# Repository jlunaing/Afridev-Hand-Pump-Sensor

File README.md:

# Monitoring System for the Afridev Hand Pump

## Overview

[Source code](src), [circuit schematic and board files](pcb), and [**technical report**](docs) of a proof-of-concept electronic system to monitor the status of the Afridev model of hand pumps.

## Introduction

Different companies, non-profit organizations, and NGOs have implemented water projects in several regions of Africa. One of the most common projects are hand pumps for water wells. A challenge that is presented once these projects are concluded and used by the local residents are that there is no regular maintenance of these hand pumps due to communication difficulties with the local communities. For instance, in most of the Democratic Republic of the Congo (DRC), the lack of cellular signal and internet connection makes it more difficult for repair teams to know when the hand pumps need repair or maintenance. 

The objective of this project is to propose a system that can reduce the time between pump failure and repair by developing a reliable failure detection measuring system that will inform a user when a pump need attention from a repair team. The system will collect data on pump usage and water flow rate estimation to be accessed remotely.

The reduction in hand pump repair time would increase the consistency of well water available to people in the remote areas like the DRC.

## Technical Background

Currently, there are no commercially available options for well pump sensors with the capabilities to detect pump function, monitor water flow rate, and transmit data internationally. However, open-source systems of a similar nature have been developed by other organizations. A notable one is [Charity: Water](https://www.charitywater.org/), a non-profit serving several developing countries through community water projects and sanitation efforts. Their [sensors](https://www.charitywater.org/our-work/sensors)&mdash;which can be retrofitted onto the Afridev, Tapstand, and India Mark II hand pump models&mdash;are able to collect data on the quantity of water being pumped from a well. The gathered data is transmitted to the cloud weekly via cellular networks, where it is stored, processed, and made viewable by an application running on Amazon Web Services (AWS). The Afridev model appears to have been developed from 2016 to 2020 by Intelligent Product Solutions (IPS), while the India Mark II sensor was developed in 2021 by TwistThink over the course of at least a year.

Extensive documentation for the Afridev and India Mark II models of the sensor is available on [GitHub](https://github.com/charitywater/india-mark-ii-sensor). Charity: Water's third generation Afridev hand-pump sensor expands on its predecessors with the ability to gather GPS, temperature, and device performance information. A more recent model, the India Mark II sensor, adds to these capabilities with additional stroke and humidity sensors. It costs $250 to build and maintain for its battery-limited 10-year lifespan and can collect ten million data points over a 24-hour period. This data is continually analyzed through Charity: Water's AWS backend, where personalized emails are dispatched to monitoring teams daily. Design specifications for Charity: Water's sensors are available from open source and served as an initial reference for this design.

The Charity: Water sensors all use a similar strategy to measure water flow rate. During a pumping cycle, water is brought into a chamber where its depth is measured by a series of capacitive sensors. From this, the quantity per pump&mdash;and therefore average flow rate&mdash;can be accurately estimated. While functional, this method has a few weaknesses. The capacitive sensors are highly sensitive to environmental changes such as temperature variation and require frequent (multiple per hour) automated calibrations to maintain measurement accuracy. Moreover, the sensor has an upper limit on the amount of flow it can measure per pump&mdash;any output over the chamber volume cannot be measured. With this setup, Charity: Water claims a 20% tolerance for the calculated flow rate, which was improved to 5% by IPS. More information can be found [here](https://github.com/charitywater/afridev2-sensor/blob/master/software/architecture%20and%20analysis/charity%20water%20AfriDev%20sensor%20algorithm%20v.2.pdf). 

In addition to the common water sensing strategy, both sensors also feature a cellular module to communicate with Charity: Water's cloud infrastructure, GPS to provide positioning, and battery power of undisclosed capacity. It is claimed that the India Mark II sensor can remain operational for up to ten years. While cellular communication is available in some areas of the DRC, coverage is sparce outside of urban settlements. See the [network coverage maps](https://www.gsma.com/coverage/#88) for details. This makes the use of Global System for Mobile Communications (GSM) technology difficult to implement for the pump distribution in the DRC. Satellite communication is a more reliable alternative, with coverage in the DRC by telecommunications infrastructure providers such as Globalstar, Swarm, and Astrocast. For instance, [Globalstar's satellite networks](https://www.globalstar.com/en-us/products/iot/stx3) cover the entirety of the DRC, where this monitoring sensor can be implemented.

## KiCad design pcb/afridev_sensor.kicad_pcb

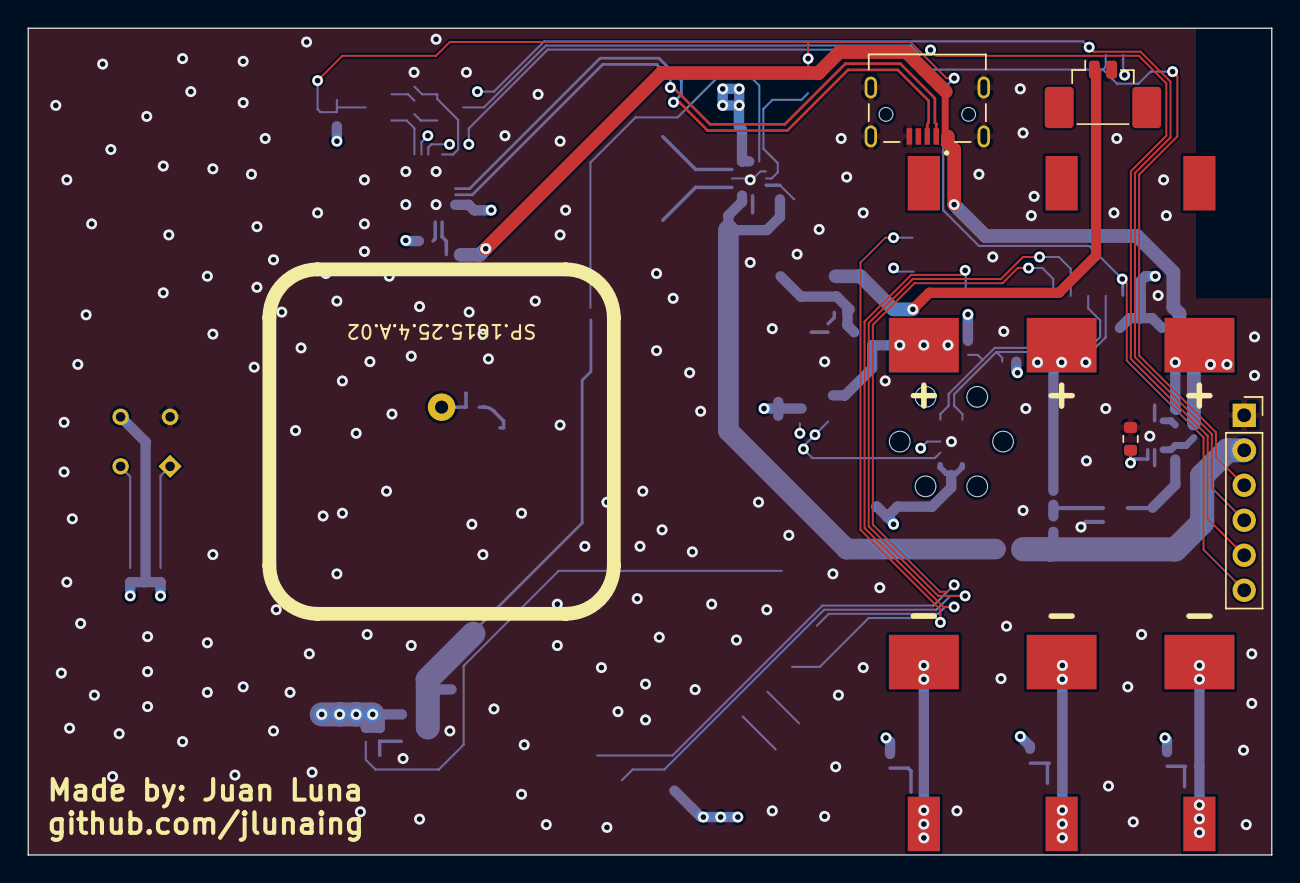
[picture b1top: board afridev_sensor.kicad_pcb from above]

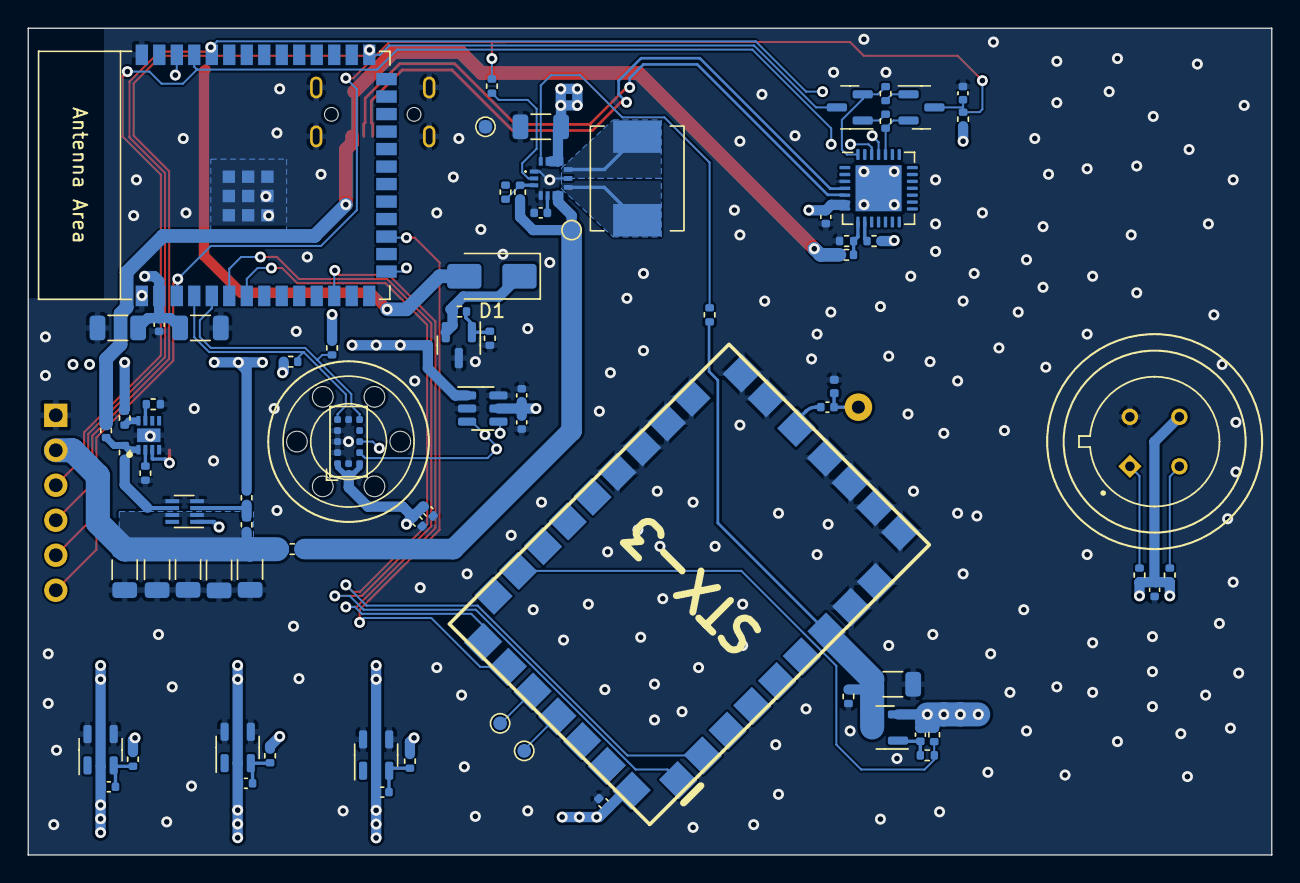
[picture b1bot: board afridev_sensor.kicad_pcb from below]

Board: 4 copper layers, 90.2 x 60.0 mm, 86 parts (78 on the bottom side), 54 nets.

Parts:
AE1: Antenna; ANT_SP.1615.25.4.A.02
BT1, BT2, BT3: Battery_Cell; Keystone 56
C1, C2, C6, C15, C17, C20, C21, C26, C28: 22uF; C_1206_3216Metric
C3, C8, C9, C10, C11, C14, C16: 0.1uF; C_0402_1005Metric
C4, C12, C18, C19, C27: 1uF; C_0402_1005Metric
C5: 4.7uF; C_0402_1005Metric
C7: 10uF; C_0402_1005Metric
C13: 33pF; C_0402_1005Metric
D1: D; D_SMA
H1: MountingHole; VlVenting
IC1: LM66200DRLR; SC-70-8
IC2: MAX77827AEFD+T; MAX77827AEFD
IC3: BQ25170DSGR; SON50P200X200X80-9N
J2: USB_B_Micro; AMPHENOL_GMCB05801124EU
L2: 33nH; L_0402_1005Metric
L4: 1uH; L_Neosid_SM-PIC0602H
M1: MLX90614ESF-AAA-000-TU; TO254P942H425-4
PROG1: Conn_01x06; PinSocket_1x06_P2.54mm_Vertical
Q1: AO3401A; SOT-23
Q2, Q3: MMBT3904; SOT-23
R1, R2, R3, R4, R7, R11, R19, R30, R31: 10K; R_0402_1005Metric
R6, R10, R14: 100; R_0402_1005Metric
R8, R15, R25, R26, R27, R28, R29, R33: 0; R_0402_1005Metric
R9: 1M; R_0402_1005Metric
R12, R13, R23: 100K; R_0402_1005Metric
R16: 510K; R_0402_1005Metric
R20: 22K; R_0402_1005Metric
R21, R24: 33K; R_0402_1005Metric
R22: 2K; R_0402_1005Metric
R32: 75K; R_0402_1005Metric
SC1: Solar Cell; Molex_PicoBlade_53398-0271_1x02-1MP_P1.25mm_Vertical
TH1: Temp; R_0603_1608Metric
TP3: TEST2; TestPoint_Pad_D1.0mm
TP4: TEST1; TestPoint_Pad_D1.0mm
TP5: PROG_VCC; TestPoint_Pad_D1.0mm
TP6: PROG_GND; TestPoint_Pad_D1.0mm
U1: VL53L4CD; ST_VL53L1x
U2: CJ431; SOT-23
U3: MCP3425A0T-ECH; SOT-23-6
U4, U5, U7: XB8358D0; SOT-23-5
U6: STX3
U9: CP2102N-Axx-xQFN28; QFN-28-1EP_5x5mm_P0.5mm_EP3.35x3.35mm
U10: ESP32-S2-SOLO

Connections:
+3V0: C15.1, Q1.3 (D), R12.1, R13.1, U6.7 (VRF)
+3V3: C3.1, C4.1, C5.1, C7.1, C8.1, C11.1, C12.1, C16.1, C17.1, C20.1, C21.1, C27.1, IC2.12 (OUT), IC2.13 (OUTS), M1.3 (VDD), Q1.2 (S), R1.1, R2.1, R3.1, R4.1, R7.1, R9.1, R19.1, U1.1 (AVDDVCSEL), U1.11 (AVDD), U3.5 (Vdd), U6.32 (VDIG), U9.6 (VDD), U9.7 (VREGIN), U10.2 (3V3)
/BN1: BT1.2 (-), C9.2, U4.2 (BAT-)
/BN2: BT2.2 (-), C10.2, U5.2 (BAT-)
/BN3: BT3.2 (-), C14.2, U7.2 (BAT-)
/BOOT: PROG1.5, Q3.3 (C), U10.27 (GPIO0)
/DN: J2.2 (D-), U9.5 (D-)
/DP: J2.3 (D+), U9.4 (D+)
/DTR: Q3.2 (E), R31.2, U9.28 (~DTR)
/EN: C18.1, PROG1.6, Q2.3 (C), R7.2, R8.1, U10.3 (EN)
/FPWM: IC2.14 (FPWM), R12.2
/LIDAR_IRQ: R2.2, U1.7 (GPIO1), U10.5 (GPIO5/TOUCH5/ADC1_CH4)
/LIDAR_XSHUT: R1.2, U1.5 (XSHUT), U10.4 (GPIO4/TOUCH4/ADC1_CH3)
/LX1: IC2.8 (LX1), L4.2
/LX2: IC2.10 (LX2), L4.1
/PGOOD: IC2.2 (POK), R8.2
/PWR_EN: R9.2, R11.2, U6.24 (PWR_EN)
/RF_ANT: AE1.1 (A), C13.2, L2.1
/RF_OUT: C13.1, U6.14 (RFOUT)
/RTS: Q2.2 (E), R30.2, U9.24 (~RTS)
/RXD: PROG1.3, U9.26 (TXD), U10.36 (U0RXD/GPIO44/CLK_OUT2)
/SCL: M1.1 (SCL/VZ), R4.2, U1.10 (SCL), U3.3 (SCL), U10.38 (GPIO2/TOUCH2/ADC1_CH1)
/SDA: M1.2 (SDA/PWM), R3.2, U1.9 (SDA), U3.4 (SDA), U10.15 (GPIO3/TOUCH3/ADC1_CH2)
/TXD: PROG1.4, U9.25 (RXD), U10.37 (U0TXD/GPIO43/CLK_OUT1)
/U1CTS: U6.1 (CTS), U10.6 (GPIO6/TOUCH6/ADC1_CH5)
/U1RTS: U6.2 (RTS), U10.7 (GPIO7/TOUCH7/ADC1_CH6)
/U1RX: U6.26 (TX), U10.12 (GPIO8/TOUCH8/ADC1_CH7)
/U1TX: U6.27 (RX), U10.17 (GPIO9/TOUCH9/ADC1_CH8/FSPIHD)
/VBUS: J2.1 (VBUS), R20.1, R28.1
/VCC_BAT: BT1.1 (+), BT2.1 (+), BT3.1 (+), D1.1 (K), R6.2, R10.2, R14.2, R24.1, R27.2, R33.1, U2.2 (K), U3.1 (Vin+)
/VCC_REG: IC2.7 (IN), R16.2, R25.2, TP5.1
/VCC_SW: C1.1, C2.1, C6.1, C26.1, C28.1, IC1.2 (VOUT_1), IC1.7 (VOUT_2), PROG1.2, R25.1, R29.2
GND: C1.2, C2.2, C3.2, C4.2, C5.2, C6.2, C7.2, C8.2, C12.2, C15.2, C16.2, C17.2, C18.2, C19.2, C20.2, C21.2, C26.2, C27.2, C28.2, IC1.1 (GND_1), IC1.4 (~ON), IC1.5 (GND_2), IC2.1 (SEL), IC2.4 (AGND), IC2.9 (PGND), IC3.4 (GND), IC3.9 (EP), J2.5 (GND), J2.6 (Shield), L2.2, M1.4 (VSS), PROG1.1, R13.2, R21.2, R22.2, R23.2, R32.2, SC1.2 (-), TH1.2, TP6.1, U1.2 (AVSSVCSEL), U1.3 (GND), U1.4 (GND), U1.6 (GND), U1.12 (GND), U2.3 (A), U3.2 (Vss), U3.6 (Vin-), U4.4 (GND), U4.5 (GND), U5.4 (GND), U5.5 (GND), U6.8 (GND), U6.9 (GND), U6.10 (GND), U6.11 (GND), U6.12 (GND), U6.13 (GND), U6.15 (GND), U6.16 (GND), U6.17 (GND), U6.18 (GND), U6.19 (GND), U6.20 (GND), U7.4 (GND), U7.5 (GND), U9.3 (GND), U9.29 (GND), U10.1 (GND), U10.40 (GND), U10.41 (GND)
unnamed: D1.2 (A), SC1.1 (+)
unnamed: IC1.3 (VIN1), R29.1, R33.2
unnamed: IC1.6 (VIN2), R26.2
unnamed: C19.1, IC2.5 (BIAS)
unnamed: IC2.3 (EN), R15.2, R16.1
unnamed: IC3.1 (IN), R26.1, R28.2
unnamed: IC3.2 (ISET), R22.1
unnamed: IC3.8 (OUT), R27.1
unnamed: IC3.3 (TS), TH1.1
unnamed: IC3.7 (VSET), R23.1
unnamed: C11.2, Q1.1 (G), R11.1
unnamed: Q2.1 (B), R31.1
unnamed: Q3.1 (B), R30.1
unnamed: R24.2, R32.1, U2.1 (REF)
unnamed: C9.1, R6.1, U4.3 (VDD)
unnamed: C10.1, R10.1, U5.3 (VDD)
unnamed: TP4.1, U6.29 (TEST1)
unnamed: TP3.1, U6.28 (TEST2)
unnamed: C14.1, R14.1, U7.3 (VDD)
unnamed: R20.2, R21.1, U9.8 (VBUS)
unnamed: R19.2, U9.9 (~RST)

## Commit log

2023-03-16 Updated circuit schematic with main components
2023-04-21 CAD Model of Housing
    First iteration of 3D model of the housing for the electronics.
2023-04-22 Updated CAD model for housing
2023-07-11 Code and CAD update
    Functioning version of demo code and updated CAD files and drawings.
2023-07-11 Comments and PlatformioIO configuration file added
2023-07-25 Update with schematic and board files
2023-08-03 Documentation update
2023-08-03 Updated images in documentation
2023-08-03 Fixed display issues with images
2023-08-03 Fixed display issues
2023-08-03 Update README.md
    Fixed display issues
